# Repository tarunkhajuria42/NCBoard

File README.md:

# NCBoard
A numeric controller Board for 2D and 3D Plotting and Printing

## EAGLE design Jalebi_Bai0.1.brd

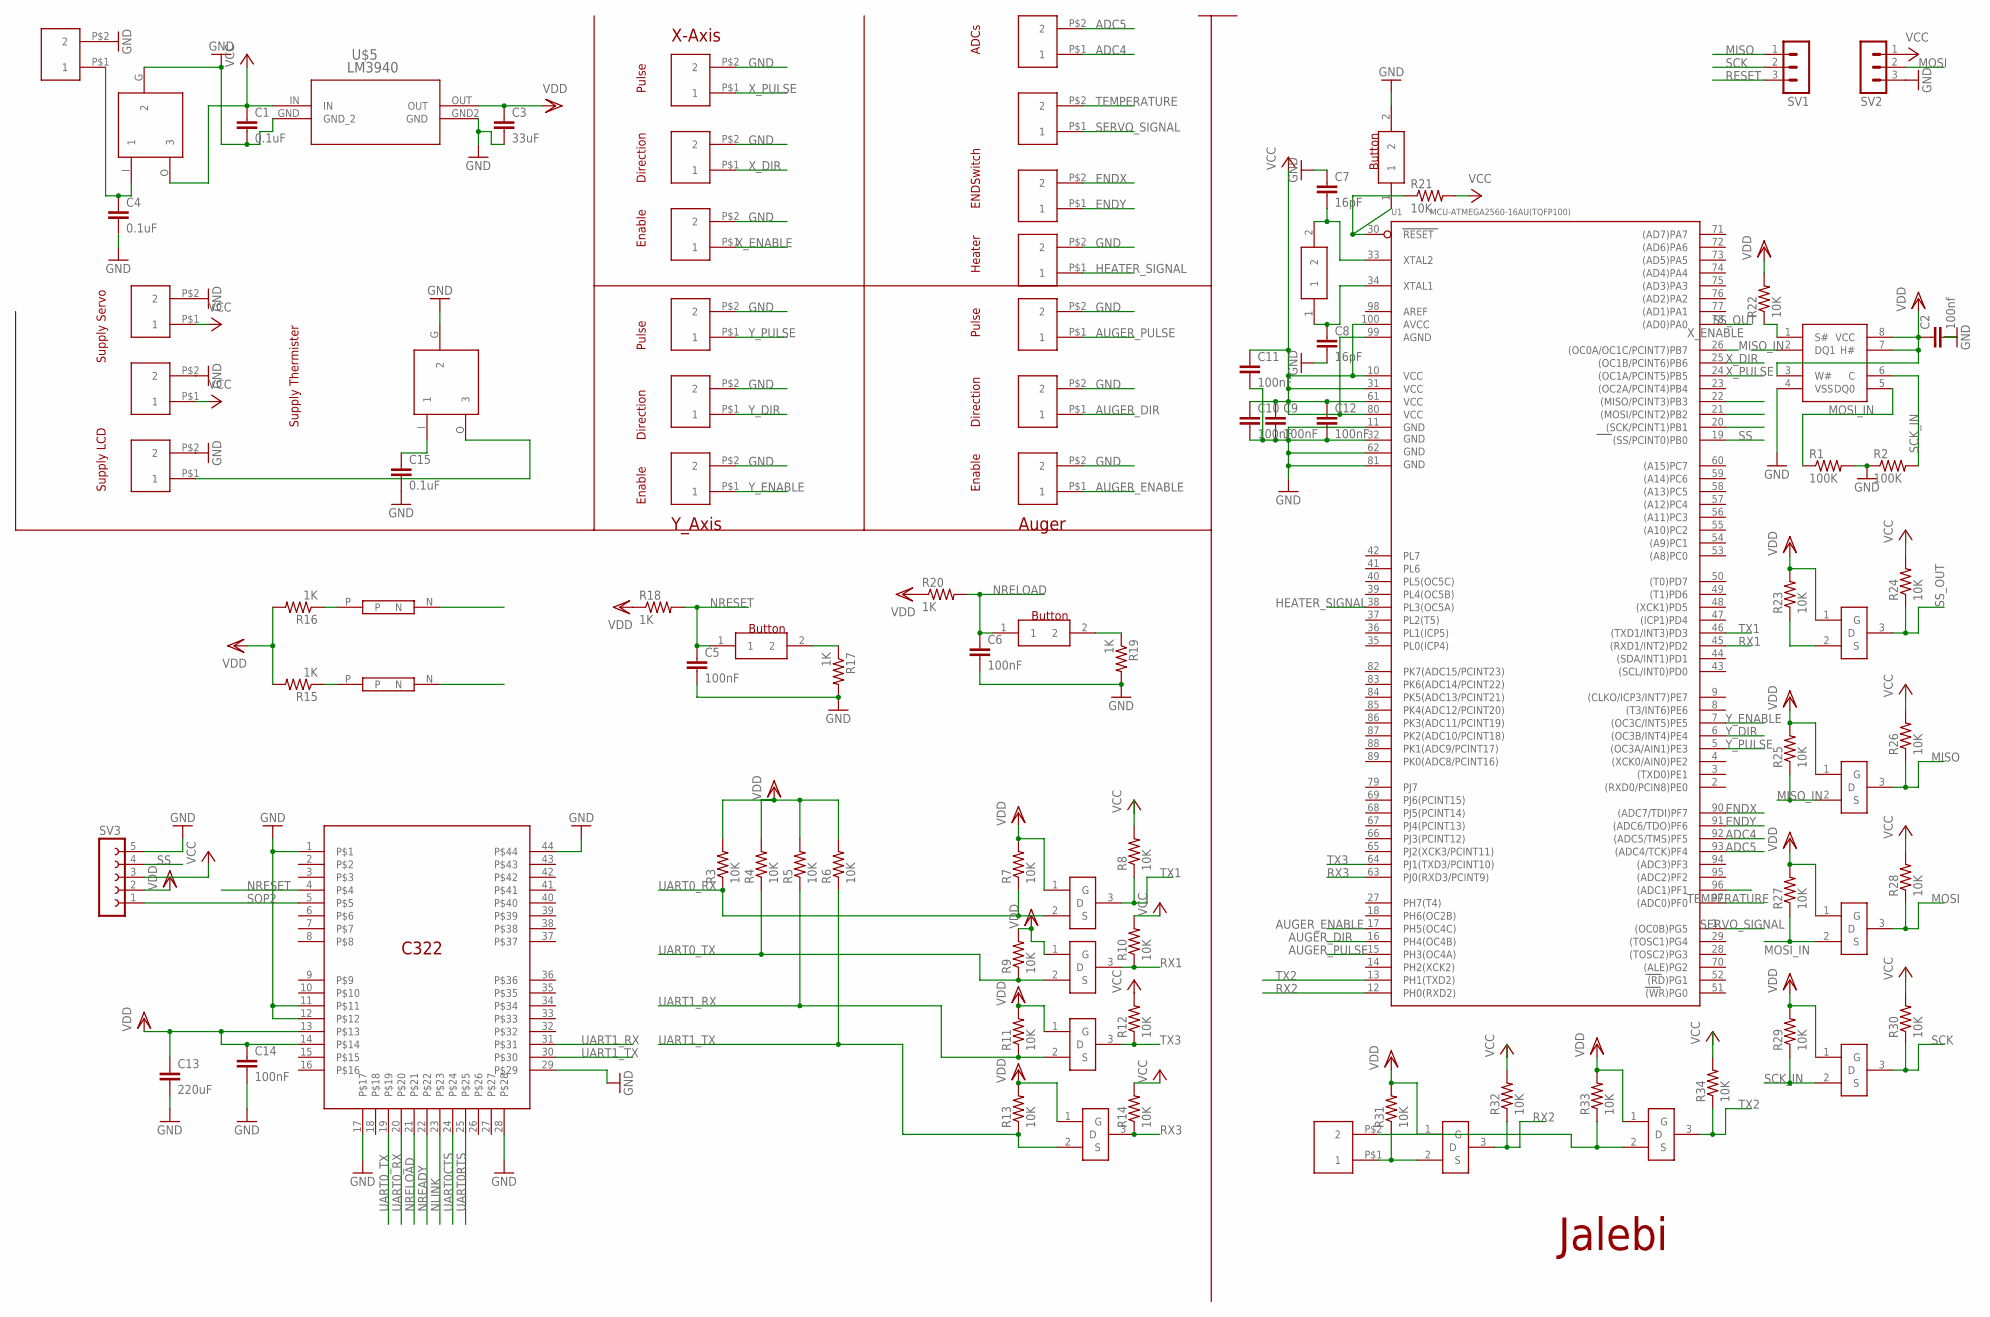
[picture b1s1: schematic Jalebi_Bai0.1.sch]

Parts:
C1, C4, C15: 0.1uF; C0805
C2: 100nf; C0805
C3: 33uF; C0805
C5, C6, C9, C10, C11, C12, C14: 100nF; C0805
C7, C8: 16pF; C0805
C13: 220uF; C0805
R1, R2: 100K; R0805
R3, R4, R5, R6, R7, R8, R9, R10, R11, R12, R13, R14, R21, R22, R23, R24, R25, R26, R27, R28, R29, R30, R31, R32, R33, R34: 10K; R0805
R15, R16, R17, R18, R19, R20: 1K; R0805
SUPPLY_LCD: TERMINALBLOCK2PIN; TERMINALBLOCK2
SUPPLY_SERVO: TERMINALBLOCK2PIN; TERMINALBLOCK2
SUPPLY_THERMISTER: TERMINALBLOCK2PIN; TERMINALBLOCK2
SV1, SV2: MA03-1
SV3: FE05-1
U1: MCU-ATMEGA2560-16AU(TQFP100); TQFP100-0.5-14X14MM
U$1: C322STD; C322
U$2, U$25: 7805
U$3, U$14, U$23, U$24, U$26, U$27, U$28, U$29, U$30, U$31, U$32, U$34, U$35, U$36, U$37: TERMINALBLOCK2PIN; TERMINALBLOCK2
U$4: FLASHM25PX80; SO08
U$5: LM3940; MP04A
U$6, U$7, U$8, U$9, U$17, U$18, U$19, U$20, U$21, U$22: BSS138; SOT23
U$10, U$11: LED(805)
U$12, U$13, U$16: BUTTON
U$15: CRYSTAL

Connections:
ADC4: U1.92 ((ADC5/TMS)PF5), U$24.P$1 (1)
ADC5: U1.93 ((ADC4/TCK)PF4), U$24.P$2 (2)
AUGER_DIR: U1.16 (PH4(OC4B)), U$36.P$1 (1)
AUGER_ENABLE: U1.17 (PH5(OC4C)), U$37.P$1 (1)
AUGER_PULSE: U1.15 (PH3(OC4A)), U$35.P$1 (1)
ENDX: U1.90 ((ADC7/TDI)PF7), U$23.P$2 (2)
ENDY: U1.91 ((ADC6/TDO)PF6), U$23.P$1 (1)
GND: C1.2, C2.2, C3.2, C4.2, C5.2, C6.2, C7.1, C8.2, C9.2, C10.2, C11.2, C12.2, C13.2, C14.2, C15.2, R1.2, R2.1, R17.2, R19.2, SUPPLY_LCD.P$2 (2), SUPPLY_SERVO.P$2 (2), SUPPLY_THERMISTER.P$2 (2), SV2.3, SV3.5, U1.11 (GND), U1.32 (GND1), U1.62 (GND2), U1.81 (GND3), U$1.1, U$1.11, U$1.12, U$1.17, U$1.28, U$1.29, U$1.44, U$2.G (2), U$3.P$2 (2), U$4.4 (VSS), U$5.GND (GND_2), U$5.GND2 (GND), U$16.2, U$25.G (2), U$26.P$2 (2), U$27.P$2 (2), U$28.P$2 (2), U$29.P$2 (2), U$30.P$2 (2), U$31.P$2 (2), U$34.P$2 (2), U$35.P$2 (2), U$36.P$2 (2), U$37.P$2 (2)
HEATER_SIGNAL: U1.38 (PL3(OC5A)), U$34.P$1 (1)
MISO: R26.1, SV1.1, U1.22 ((MISO/PCINT3)PB3), U$18.3 (D)
MISO_IN: R25.1, U$4.2 (DQ1), U$18.2 (S)
MOSI: R28.1, SV2.2, U1.21 ((MOSI/PCINT2)PB2), U$19.3 (D)
MOSI_IN: R1.1, R27.1, U$4.5 (DQ0), U$19.2 (S)
unnamed: SUPPLY_LCD.P$1 (1), U$25.O (3)
unnamed: C4.1, C15.1, U$2.I (1), U$3.P$1 (1), U$25.I (1)
unnamed: R15.1, U$11.P
unnamed: C7.2, U1.33 (XTAL2), U$15.2
unnamed: R16.1, U$10.P
unnamed: C8.1, U1.34 (XTAL1), U$15.1
unnamed: R17.1, U$12.2
unnamed: R19.1, U$13.2
NLINK: U$1.23, U$10.N
NREADY: U$1.22, U$11.N
NRELOAD: C6.1, R20.2, U$1.21, U$13.1
NRESET: C5.1, R18.2, U$1.4, U$12.1
RESET: R21.1, SV1.3, U1.30 (RESET), U$16.1
RX1: R10.1, U1.45 ((RXD1/INT2)PD2), U$7.3 (D)
RX2: R32.1, U1.12 (PH0(RXD2)), U$21.3 (D)
RX3: R14.1, U1.63 (PJ0(RXD3/PCINT9)), U$9.3 (D)
RX_IN: R31.1, U$14.P$1 (1), U$21.2 (S)
SCK: R30.1, SV1.2, U1.20 ((SCK/PCINT1)PB1), U$20.3 (D)
SCK_IN: R2.2, R29.1, U$4.6 (C), U$20.2 (S)
SERVO_SIGNAL: U1.1 ((OC0B)PG5), U$32.P$1 (1)
SOP2: SV3.1, U$1.5
SS: SV3.4, U1.19 ((SS/PCINT0)PB0)
SS_IN: R22.1, R23.1, U$4.1 (S#), U$17.2 (S)
SS_OUT: R24.1, U1.78 ((AD0)PA0), U$17.3 (D)
TEMPERATURE: U1.97 ((ADC0)PF0), U$32.P$2 (2)
TX1: R8.1, U1.46 ((TXD1/INT3)PD3), U$6.3 (D)
TX2: R34.1, U1.13 (PH1(TXD2)), U$22.3 (D)
TX3: R12.1, U1.64 (PJ1(TXD3/PCINT10)), U$8.3 (D)
TX_IN: R33.1, U$14.P$2 (2), U$22.2 (S)
UART0CTS: U$1.24
UART0RTS: U$1.25
UART0_RX: R3.1, R7.1, U$1.20, U$6.2 (S)
UART0_TX: R4.1, R9.1, U$1.19, U$7.2 (S)
UART1_RX: R5.1, R11.1, U$1.31, U$8.2 (S)
UART1_TX: R6.1, R13.1, U$1.30, U$9.2 (S)
VCC: C1.1, C9.1, C10.1, C11.1, C12.1, R8.2, R10.2, R12.2, R14.2, R21.2, R24.2, R26.2, R28.2, R30.2, R32.2, R34.2, SUPPLY_SERVO.P$1 (1), SUPPLY_THERMISTER.P$1 (1), SV2.1, SV3.3, U1.10 (VCC), U1.31 (VCC1), U1.61 (VCC2), U1.80 (VCC3), U1.99 (AGND), U1.100 (AVCC), U$2.O (3), U$5.IN
VDD: C2.1, C3.1, C13.1, C14.1, R3.2, R4.2, R5.2, R6.2, R7.2, R9.2, R11.2, R13.2, R15.2, R16.2, R18.1, R20.1, R22.2, R23.2, R25.2, R27.2, R29.2, R31.2, R33.2, SV3.2, U$1.13, U$1.14, U$4.3 (W#), U$4.7 (H#), U$4.8 (VCC), U$5.OUT, U$6.1 (G), U$7.1 (G), U$8.1 (G), U$9.1 (G), U$17.1 (G), U$18.1 (G), U$19.1 (G), U$20.1 (G), U$21.1 (G), U$22.1 (G)
X_DIR: U1.25 ((OC1B/PCINT6)PB6), U$27.P$1 (1)
X_ENABLE: U1.26 ((OC0A/OC1C/PCINT7)PB7), U$28.P$1 (1)
X_PULSE: U1.24 ((OC1A/PCINT5)PB5), U$26.P$1 (1)
Y_DIR: U1.6 ((OC3B/INT4)PE4), U$30.P$1 (1)
Y_ENABLE: U1.7 ((OC3C/INT5)PE5), U$31.P$1 (1)
Y_PULSE: U1.5 ((OC3A/AIN1)PE3), U$29.P$1 (1)

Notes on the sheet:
Jalebi
X-Axis
Y_Axis
Auger
Pulse
Direction
Enable
Heater
Supply LCD
Supply Servo
Supply Thermister
ENDSwitch
ADCs

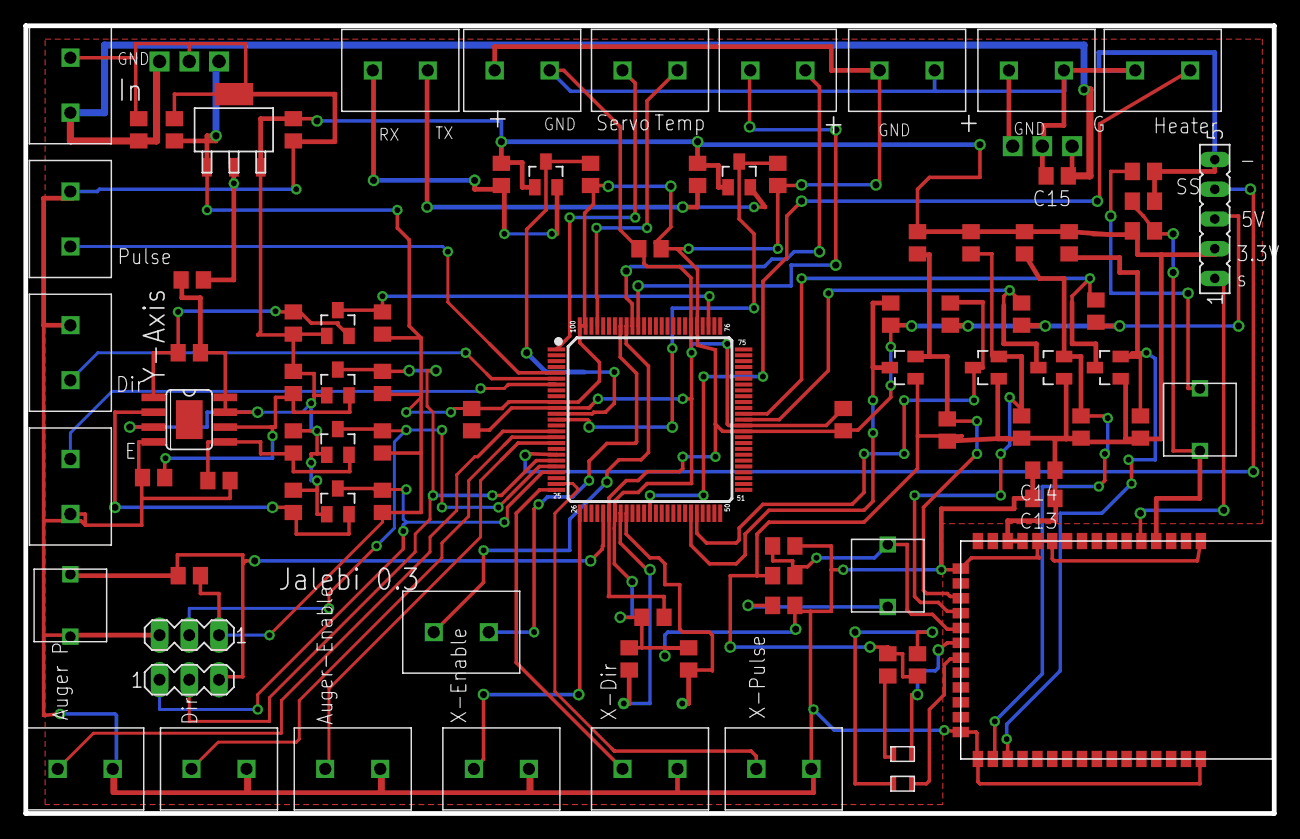
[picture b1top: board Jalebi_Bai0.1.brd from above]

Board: 2 copper layers, 106.7 x 67.3 mm, 92 parts (0 on the bottom side), 54 nets.

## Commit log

2017-03-21 Upload 0.2
